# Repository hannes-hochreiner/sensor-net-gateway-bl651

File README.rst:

SensorNet Gateway BL651
=======================

A gateway for the SensorNet project, based on the BL651 module.

.. image:: images/fully_assembled.jpg
  :alt: fully assembled board

Functional Test
---------------

+------------------+--------+
| feature          | status |
+==================+========+
| Power Management | OK     |
+------------------+--------+
| SWD              | OK     |
+------------------+--------+
| USB              | OK     |
+------------------+--------+
| LED              | OK     |
+------------------+--------+
| Sensor           | OK     |
+------------------+--------+

Firmware
--------

Firmware for this board can be found in the repository `"hannes-hochreiner/sensor-net-nrf52810-firmware" <https://github.com/hannes-hochreiner/sensor-net-nrf52810-firmware>`_

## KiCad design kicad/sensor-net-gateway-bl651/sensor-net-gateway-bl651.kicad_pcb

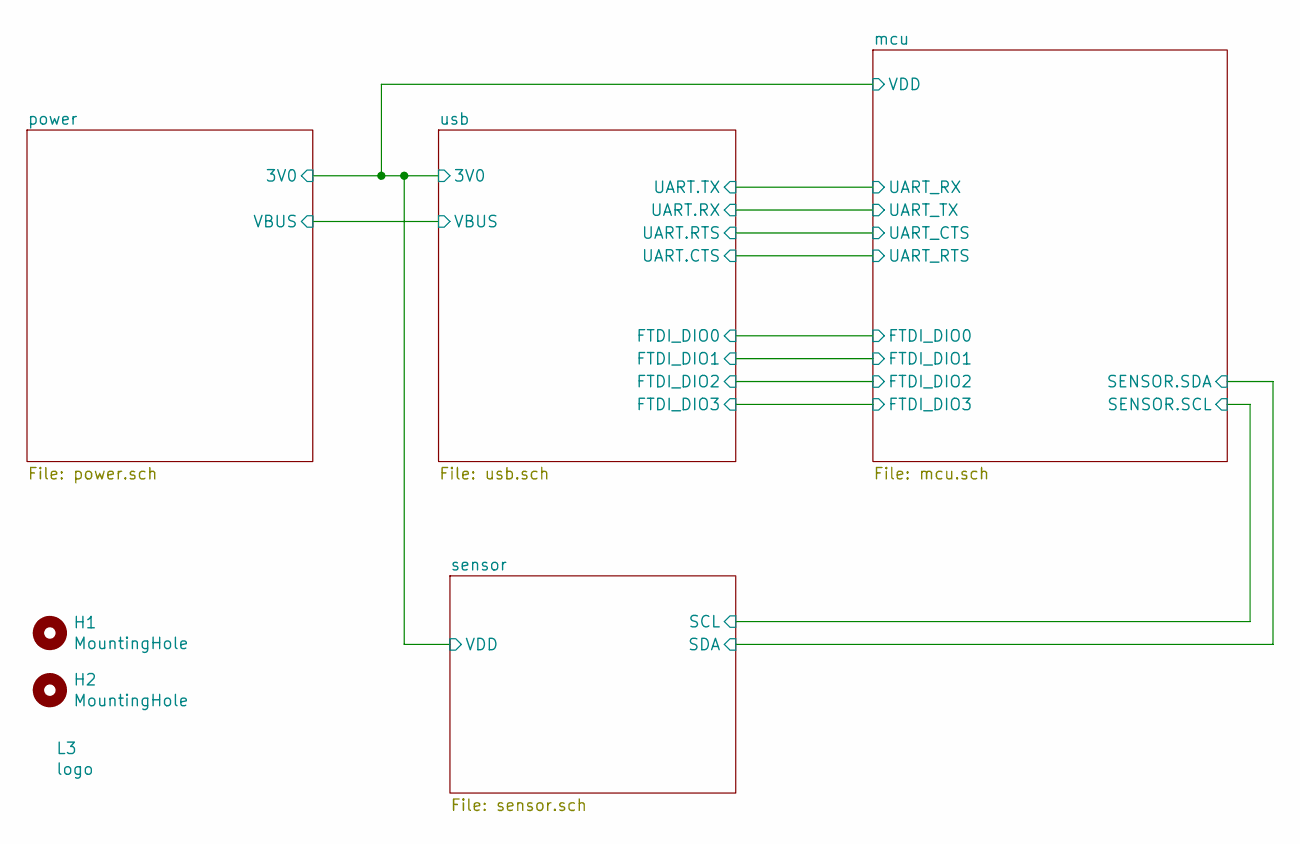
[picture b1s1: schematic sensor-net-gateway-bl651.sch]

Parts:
H1, H2: MountingHole; MountingHole_2.2mm_M2_Pad_Via
L3: logo

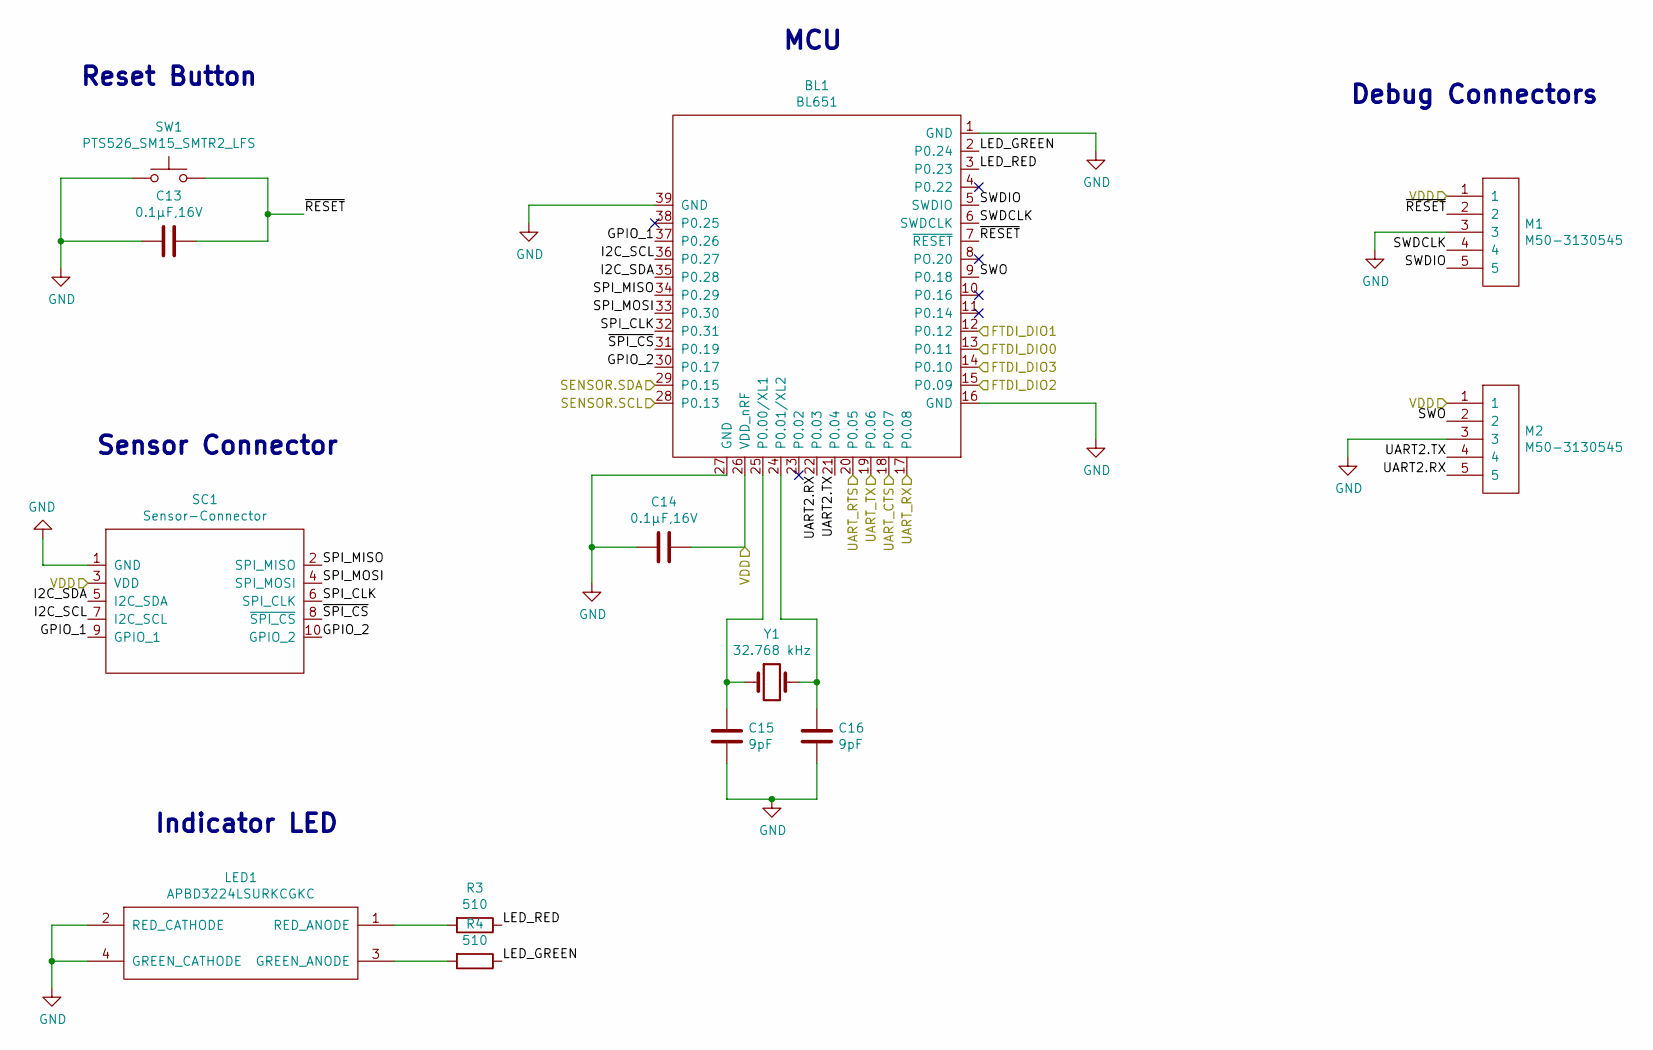
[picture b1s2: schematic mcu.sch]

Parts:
BL1: BL651; Manufacturer Part Number 453-00005; Digi-Key Part Number 453-00005CT-ND
C13, C14: 0.1µF,16V; C_0603_1608Metric
C15, C16: 9pF; C_0603_1608Metric; Manufacturer Part Number CC0603CRNPO9BN9R0; Digi-Key Part Number 311-3866-1-ND
LED1: APBD3224LSURKCGKC; Manufacturer Part Number APBD3224LSURKCGKC; Digi-Key Part Number 754-1962-1-ND
M1, M2: M50-3130545; Manufacturer_PartNumber M50-3130545; DigiKey_PartNumber 952-3585-ND
R3, R4: 510; R_0603_1608Metric; Manufacturer Part Number RR0816P-511-D; Digi-Key Part Number RR08P510DCT-ND
SC1: Sensor-Connector; Sensor-Connector_M50-3150542R; Manufacturer Part Number M50-3150542R; Digi-Key Part Number 952-3493-1-ND
SW1: PTS526_SM15_SMTR2_LFS; PTS526-SM15-SMTR2-LFS; Manufacturer Part Number PTS526 SM15 SMTR2 LFS; Digi-Key Part Number CKN12220-1-ND
Y1: 32.768 kHz; Crystal_SMD_MicroCrystal_CC7V-T1A-2Pin_3.2x1.5mm; Manufacturer Part Number CM7V-T1A-32.768KHZ-9PF-10PPM-TA-QC; Digi-Key Part Number 2195-CM7V-T1A-32.768KHZ-9PF-10PPM-TA-QC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

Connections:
/mcu/FTDI_DIO0: BL1.13 (P0.11); also elsewhere on the board
/mcu/FTDI_DIO1: BL1.12 (P0.12); also elsewhere on the board
/mcu/FTDI_DIO2: BL1.15 (P0.09); also elsewhere on the board
/mcu/FTDI_DIO3: BL1.14 (P0.10); also elsewhere on the board
/mcu/GPIO_1: BL1.37 (P0.26), SC1.9 (GPIO_1)
/mcu/GPIO_2: BL1.30 (P0.17), SC1.10 (GPIO_2)
/mcu/I2C_SCL: BL1.36 (P0.27), SC1.7 (I2C_SCL)
/mcu/I2C_SDA: BL1.35 (P0.28), SC1.5 (I2C_SDA)
/mcu/LED_GREEN: BL1.2 (P0.24), R4.1
/mcu/LED_RED: BL1.3 (P0.23), R3.1
/mcu/SPI_CLK: BL1.32 (P0.31), SC1.6 (SPI_CLK)
/mcu/SPI_MISO: BL1.34 (P0.29), SC1.2 (SPI_MISO)
/mcu/SPI_MOSI: BL1.33 (P0.30), SC1.4 (SPI_MOSI)
/mcu/SWDCLK: BL1.6 (SWDCLK), M1.4
/mcu/SWDIO: BL1.5 (SWDIO), M1.5
/mcu/SWO: BL1.9 (P0.18), M2.2
/mcu/UART2.RX: BL1.22 (P0.03), M2.5
/mcu/UART2.TX: BL1.21 (P0.04), M2.4
/mcu/~RESET: BL1.7 (~RESET), C13.1, M1.2, SW1.2
/mcu/~SPI_CS: BL1.31 (P0.19), SC1.8 (~SPI_CS)
/power/3V0: BL1.26 (VDD_nRF), C14.1, M1.1, M2.1, SC1.3 (VDD); also elsewhere on the board
/sensor/SCL: BL1.28 (P0.13); also elsewhere on the board
/sensor/SDA: BL1.29 (P0.15); also elsewhere on the board
/usb/UART.CTS: BL1.20 (P0.05); also elsewhere on the board
/usb/UART.RTS: BL1.18 (P0.07); also elsewhere on the board
/usb/UART.RX: BL1.19 (P0.06); also elsewhere on the board
/usb/UART.TX: BL1.17 (P0.08); also elsewhere on the board
GND: BL1.1 (GND), BL1.16 (GND), BL1.27 (GND), BL1.39 (GND), C13.2, C14.2, C15.2, C16.2, LED1.2 (RED_CATHODE), LED1.4 (GREEN_CATHODE), M1.3, M2.3, SC1.1 (GND), SW1.1; also elsewhere on the board
unnamed: BL1.24 (P0.01/XL2), C16.1, Y1.2
unnamed: BL1.25 (P0.00/XL1), C15.1, Y1.1
unnamed: LED1.1 (RED_ANODE), R3.2
unnamed: LED1.3 (GREEN_ANODE), R4.2

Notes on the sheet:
Indicator LED
Sensor Connector
Reset Button
MCU
Debug Connectors

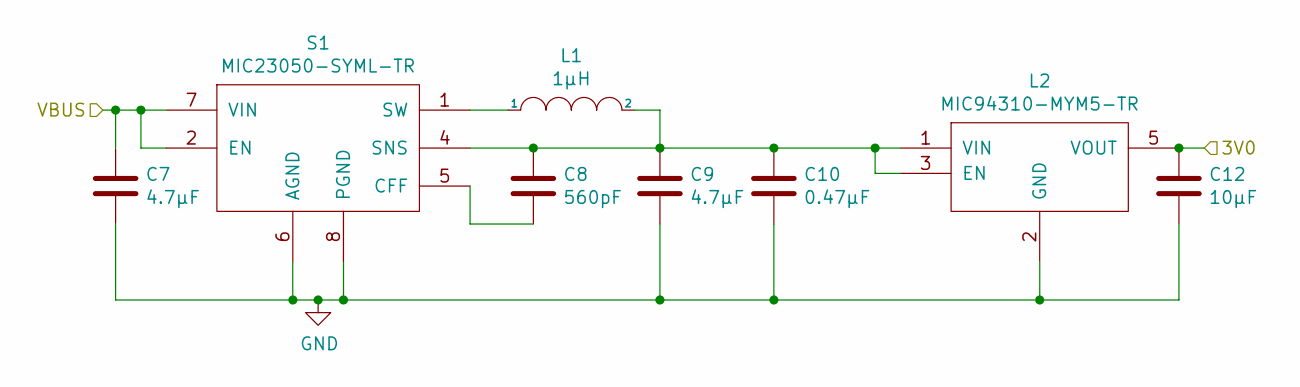
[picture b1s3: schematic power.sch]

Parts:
C7: 4.7µF; C_0603_1608Metric; Manufacturer_PartNumber CL10A475MQ8NNNC; DigiKey_PartNumber 1276-1907-1-ND
C8: 560pF; C_0603_1608Metric; DigiKey_PartNumber 1276-2315-1-ND
C9: 4.7µF; C_0603_1608Metric; DigiKey_PartNumber 1276-1907-1-ND
C10: 0.47µF; C_0603_1608Metric; DigiKey_PartNumber 1276-2082-1-ND
C12: 10µF; C_0603_1608Metric; DigiKey_PartNumber 1276-1119-1-ND
L1: 1µH; L_0805_2012Metric; DigiKey_PartNumber 445-6391-1-ND
L2: MIC94310-MYM5-TR; SOT-23-5; Manufacturer Part Number MIC94310-MYM5-TR; Digi-Key Part Number MIC94310-MYM5-CT-ND
S1: MIC23050-SYML-TR; Manufacturer Part Number MIC23050-SYML-TR; Digi-Key Part Number 576-3351-1-ND

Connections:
/power/3V0: C12.1, L2.5 (VOUT); also elsewhere on the board
/power/VBUS: C7.1, S1.2 (EN), S1.7 (VIN); also elsewhere on the board
GND: C7.2, C9.2, C10.2, C12.2, L2.2 (GND), S1.6 (AGND), S1.8 (PGND); also elsewhere on the board
unnamed: C8.2, S1.5 (CFF)
unnamed: C8.1, C9.1, C10.1, L1.2, L2.1 (VIN), L2.3 (EN), S1.4 (SNS)
unnamed: L1.1, S1.1 (SW)

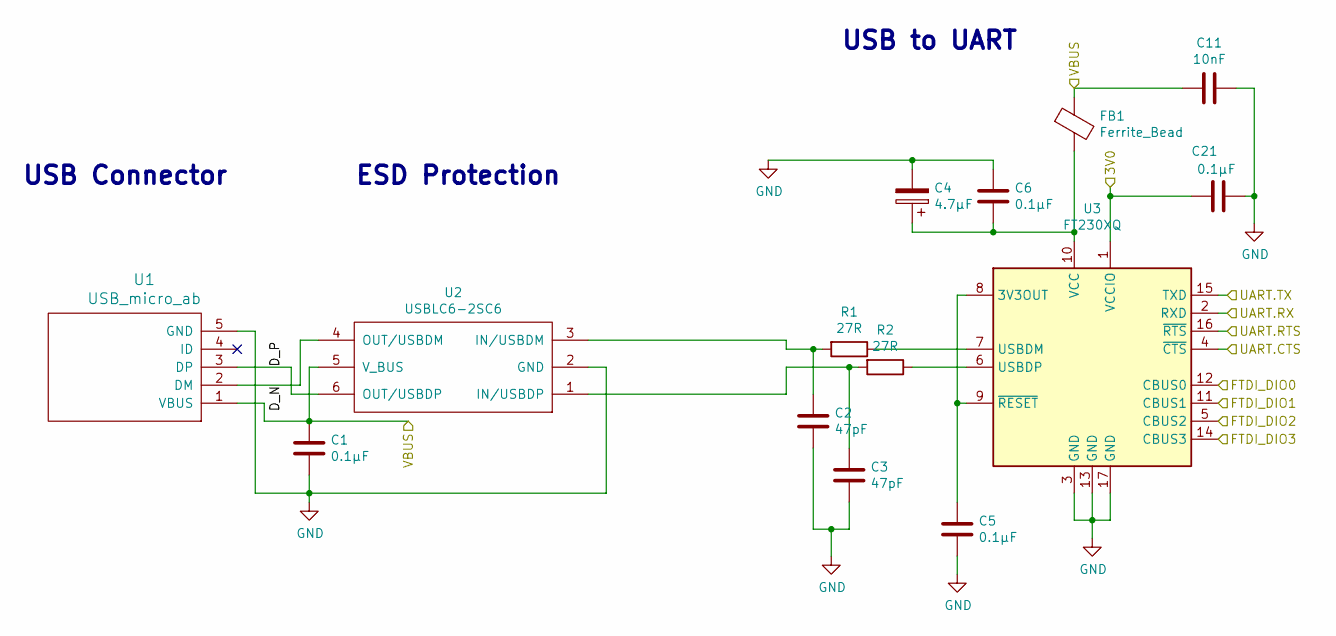
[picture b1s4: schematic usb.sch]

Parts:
C1, C5, C6, C21: 0.1µF; C_0603_1608Metric
C2, C3: 47pF; C_0603_1608Metric
C4: 4.7µF; 865080640004; Manufacturer_PartNumber 865080640004; DigiKey_PartNumber 732-8449-1-ND
C11: 10nF; C_0603_1608Metric
FB1: Ferrite_Bead; C_0805_2012Metric; Manufacturer Part Number MI0805K601R-10; Digi-Key Part Number 240-2390-1-ND
R1, R2: 27R; R_0603_1608Metric
U1: USB_micro_ab; MOLEX_USB_MICRO_0475890001; Manufacturer Part Number 0475890001; Digi-Key Part Number WM17143CT-ND
U2: USBLC6-2SC6; USBLC6-2SC6_SOT-23-6; Manufacturer Part Number USBLC6-2SC6; Digi-Key Part Number 497-5235-1-ND
U3: FT230XQ; QFN-16-1EP_4x4mm_P0.65mm_EP2.1x2.1mm; Manufacturer Part Number FT230XQ-R; Digi-Key Part Number 768-1130-1-ND

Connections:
/mcu/FTDI_DIO0: U3.12 (CBUS0); also elsewhere on the board
/mcu/FTDI_DIO1: U3.11 (CBUS1); also elsewhere on the board
/mcu/FTDI_DIO2: U3.5 (CBUS2); also elsewhere on the board
/mcu/FTDI_DIO3: U3.14 (CBUS3); also elsewhere on the board
/power/3V0: C21.1, U3.1 (VCCIO); also elsewhere on the board
/power/VBUS: C1.1, C11.1, FB1.1, U1.1 (VBUS), U2.5 (V_BUS); also elsewhere on the board
/usb/D_N: U1.2 (DM), U2.4 (OUT/USBDM)
/usb/D_P: U1.3 (DP), U2.6 (OUT/USBDP)
/usb/UART.CTS: U3.4 (~CTS); also elsewhere on the board
/usb/UART.RTS: U3.16 (~RTS); also elsewhere on the board
/usb/UART.RX: U3.2 (RXD); also elsewhere on the board
/usb/UART.TX: U3.15 (TXD); also elsewhere on the board
GND: C1.2, C2.2, C3.2, C4.2, C5.2, C6.1, C11.2, C21.2, U1.5 (GND), U2.2 (GND), U3.3 (GND), U3.13 (GND), U3.17 (GND); also elsewhere on the board
unnamed: C2.1, R1.2, U2.3 (IN/USBDM)
unnamed: C3.1, R2.2, U2.1 (IN/USBDP)
unnamed: C4.1, C6.2, FB1.2, U3.10 (VCC)
unnamed: C5.1, U3.8 (3V3OUT), U3.9 (~RESET)
unnamed: R1.1, U3.7 (USBDM)
unnamed: R2.1, U3.6 (USBDP)

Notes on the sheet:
USB Connector
ESD Protection
USB to UART

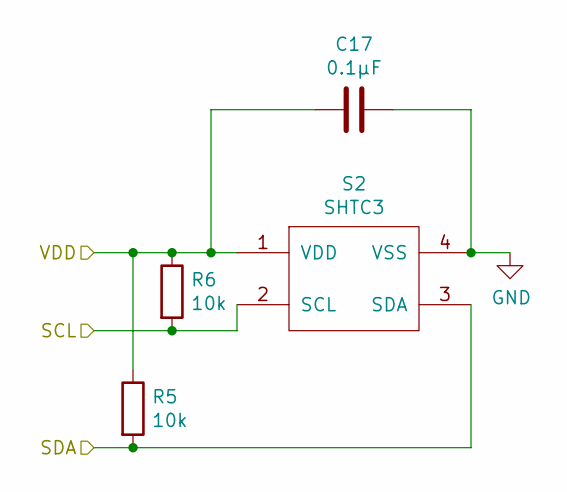
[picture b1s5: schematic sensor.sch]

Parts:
C17: 0.1µF; C_0603_1608Metric
R5, R6: 10k; R_0603_1608Metric
S2: SHTC3; Manufacturer Part Number SHTC3; Digi-Key Part Number 1649-1105-1-ND

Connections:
/power/3V0: C17.2, R5.1, R6.1, S2.1 (VDD); also elsewhere on the board
/sensor/SCL: R6.2, S2.2 (SCL); also elsewhere on the board
/sensor/SDA: R5.2, S2.3 (SDA); also elsewhere on the board
GND: C17.1, S2.4 (VSS); also elsewhere on the board

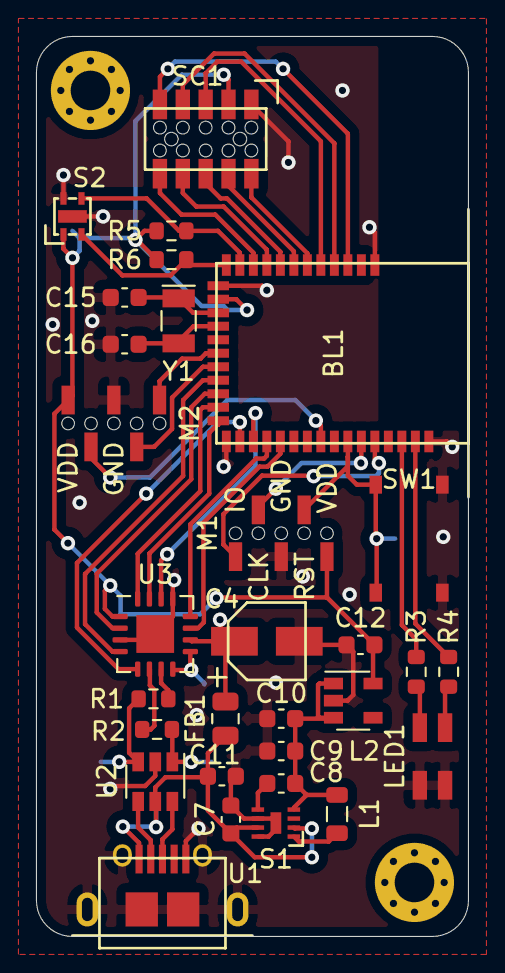
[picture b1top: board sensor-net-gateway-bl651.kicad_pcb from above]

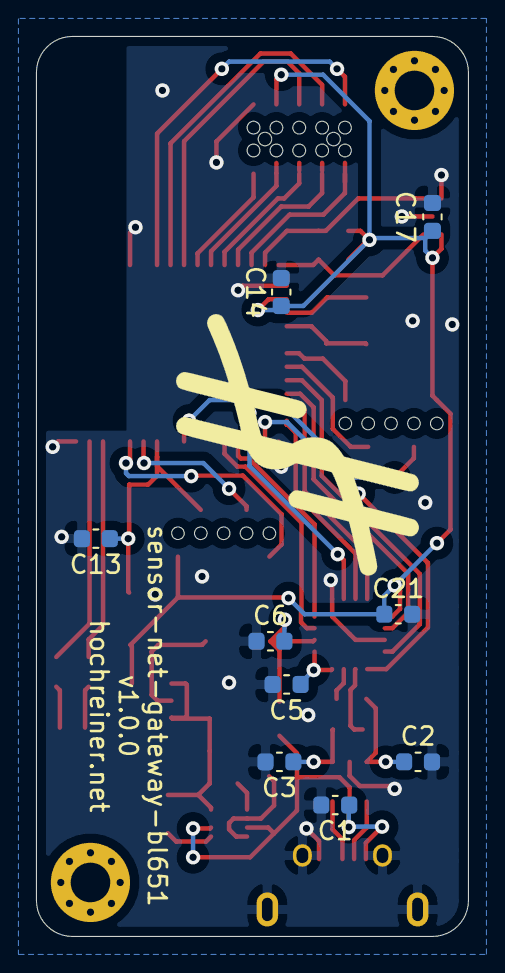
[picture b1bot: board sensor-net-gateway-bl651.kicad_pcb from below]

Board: 2 copper layers, 24.0 x 50.0 mm, 42 parts (10 on the bottom side), 44 nets.

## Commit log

2020-10-18 added a README
2020-10-18 started schematic
2020-10-19 added power and usb2uart
2020-10-20 started layout
2020-10-25 routing snapshot
2020-10-25 added pin descriptions
2020-10-25 added BOM
2020-11-08 added image and tests
2020-11-08 started work on firmware
2020-11-12 refactored sensor code
2020-11-12 added radio
2020-11-14 moved firmware to a separate repository
2020-11-21 add case
2020-11-21 update model
2020-11-22 add hole for sensor
2020-11-22 update pcb model
2020-11-22 update pcb mount
2020-11-22 add order file
